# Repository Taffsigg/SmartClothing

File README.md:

# SmartClothing
the shirt that detects heart attacks

//short description of project

//file directory links

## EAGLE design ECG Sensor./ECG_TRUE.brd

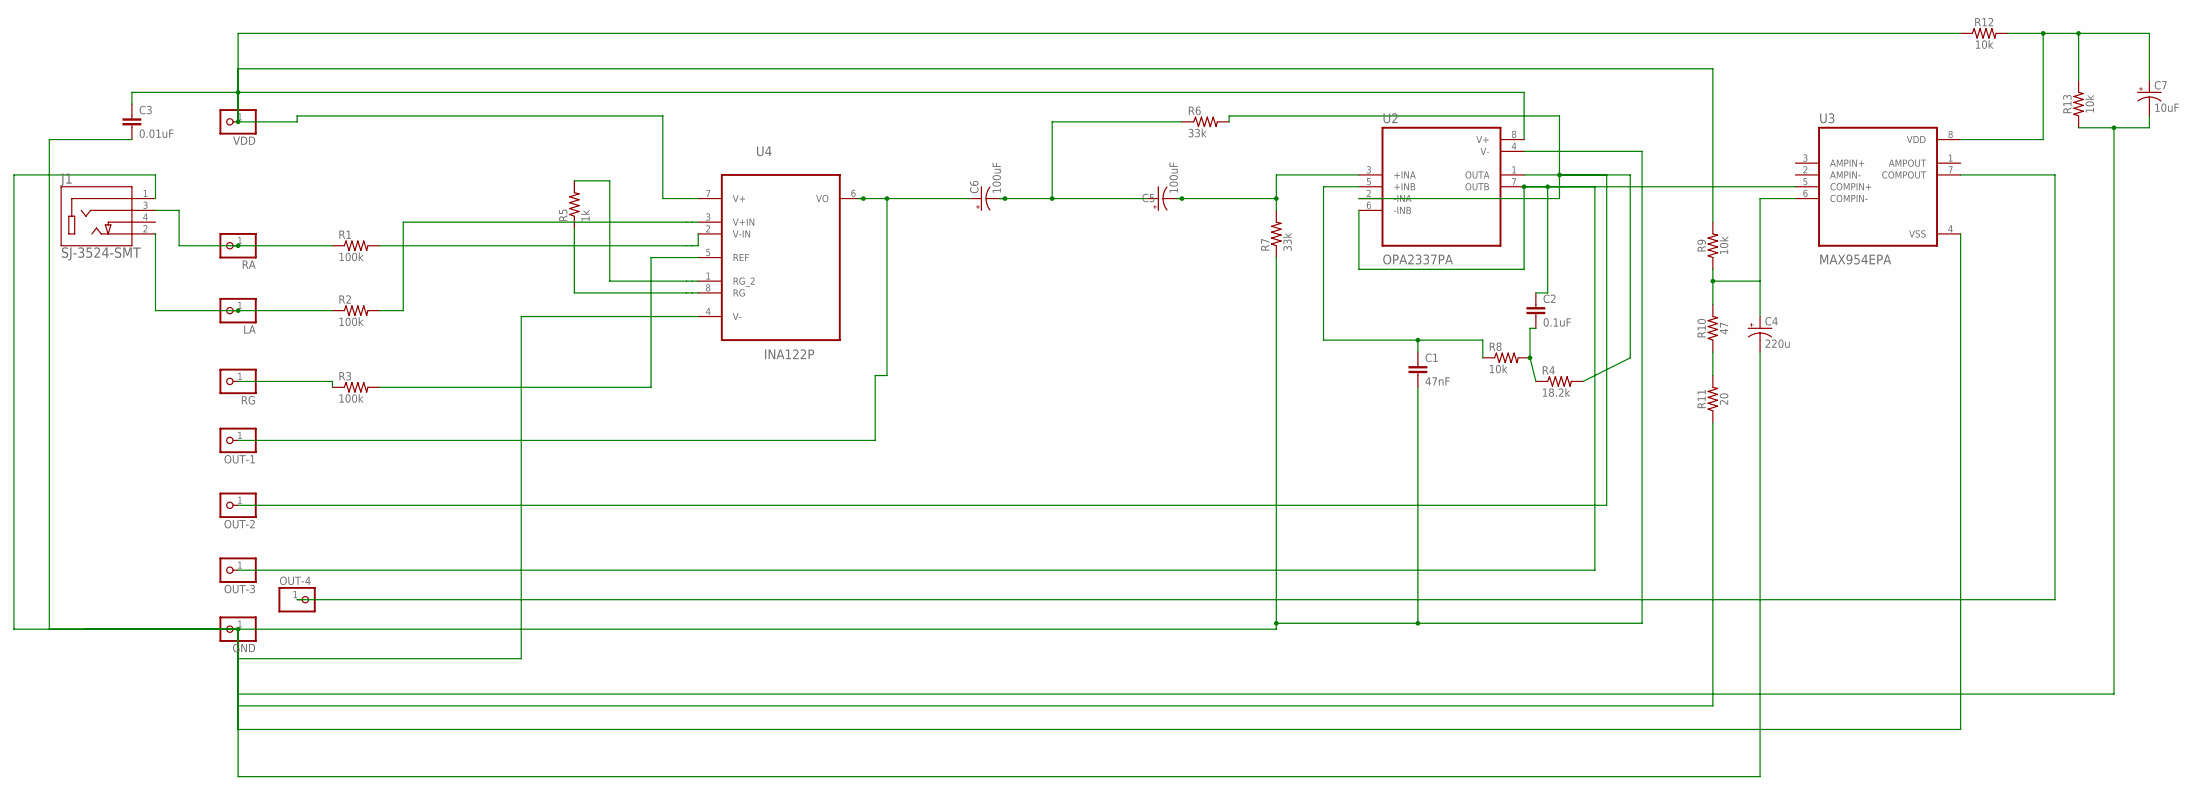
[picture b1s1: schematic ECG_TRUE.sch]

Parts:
C1: 47nF; CAP-PTH-SMALL-KIT
C2: 0.1uF; CAP-PTH-SMALL-KIT
C3: 0.01uF; CAP-PTH-SMALL-KIT
C4: 220u; E3,5-10
C5, C6: 100uF; CPOL-RADIAL-2.5MM-6.5MM
C7: 10uF; CPOL-RADIAL-2.5MM-5MM-KIT
GND: PINHD-1X1; 1X01
J1: SJ-3524-SMT; CUI_SJ-3524-SMT
LA: PINHD-1X1; 1X01
OUT-1, OUT-2, OUT-3, OUT-4: PINHD-1X1; 1X01
R1, R2, R3: 100k; AXIAL-0.3-KIT
R4: 18.2k; AXIAL-0.3-KIT
R5: 1k; AXIAL-0.3-KIT
R6, R7: 33k; AXIAL-0.3-KIT
R8, R9: 10k; AXIAL-0.3-KIT
R10: 47; AXIAL-0.3-KIT
R11: 20; AXIAL-0.3-KIT
R12, R13: 10k; AXIAL-0.3
RA: PINHD-1X1; 1X01
RG: PINHD-1X1; 1X01
U2: OPA2337PA; DIP794W45P254L1060H508Q8
U3: MAX954EPA; DIP794W47P254L991H457Q8
U4: INA122P; DIP254P762X508-8
VDD: PINHD-1X1; 1X01

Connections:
unnamed: J1.3, R1.P$1 (1), RA.1
unnamed: C7.1 (+), R12.P$2 (2), R13.P$2 (2), U3.8 (VDD)
unnamed: C2.2, R4.P$1 (1), R8.P$2 (2)
unnamed: R1.P$2 (2), U4.2 (V-IN)
unnamed: R2.P$2 (2), U4.3 (V+IN)
unnamed: R3.P$1 (1), RG.1
unnamed: R3.P$2 (2), U4.5 (REF)
unnamed: C6.1 (+), OUT-1.1, U4.6 (VO)
unnamed: R5.P$2 (2), U4.1 (RG_2)
unnamed: R5.P$1 (1), U4.8 (RG)
unnamed: C5.1 (+), C6.2 (-), R6.P$1 (1)
unnamed: C5.2 (-), R7.P$2 (2), U2.3 (+INA)
unnamed: OUT-2.1, R4.P$2 (2), R6.P$2 (2), U2.1 (OUTA), U2.2 (-INA)
unnamed: C3.1, R9.P$2 (2), R12.P$1 (1), U2.8 (V+), U4.7 (V+), VDD.1
unnamed: C2.1, OUT-3.1, U2.6 (-INB), U2.7 (OUTB), U3.5 (COMPIN+)
unnamed: R10.P$1 (1), R11.P$2 (2)
unnamed: C1.1, R8.P$1 (1), U2.5 (+INB)
unnamed: C4.+, R9.P$1 (1), R10.P$2 (2), U3.6 (COMPIN-)
unnamed: OUT-4.1, U3.7 (COMPOUT)
unnamed: J1.2, LA.1, R2.P$1 (1)
unnamed: C1.2, C3.2, C4.-, C7.2 (-), GND.1, J1.1, R7.P$1 (1), R11.P$1 (1), R13.P$1 (1), U2.4 (V-), U3.4 (VSS), U4.4 (V-)

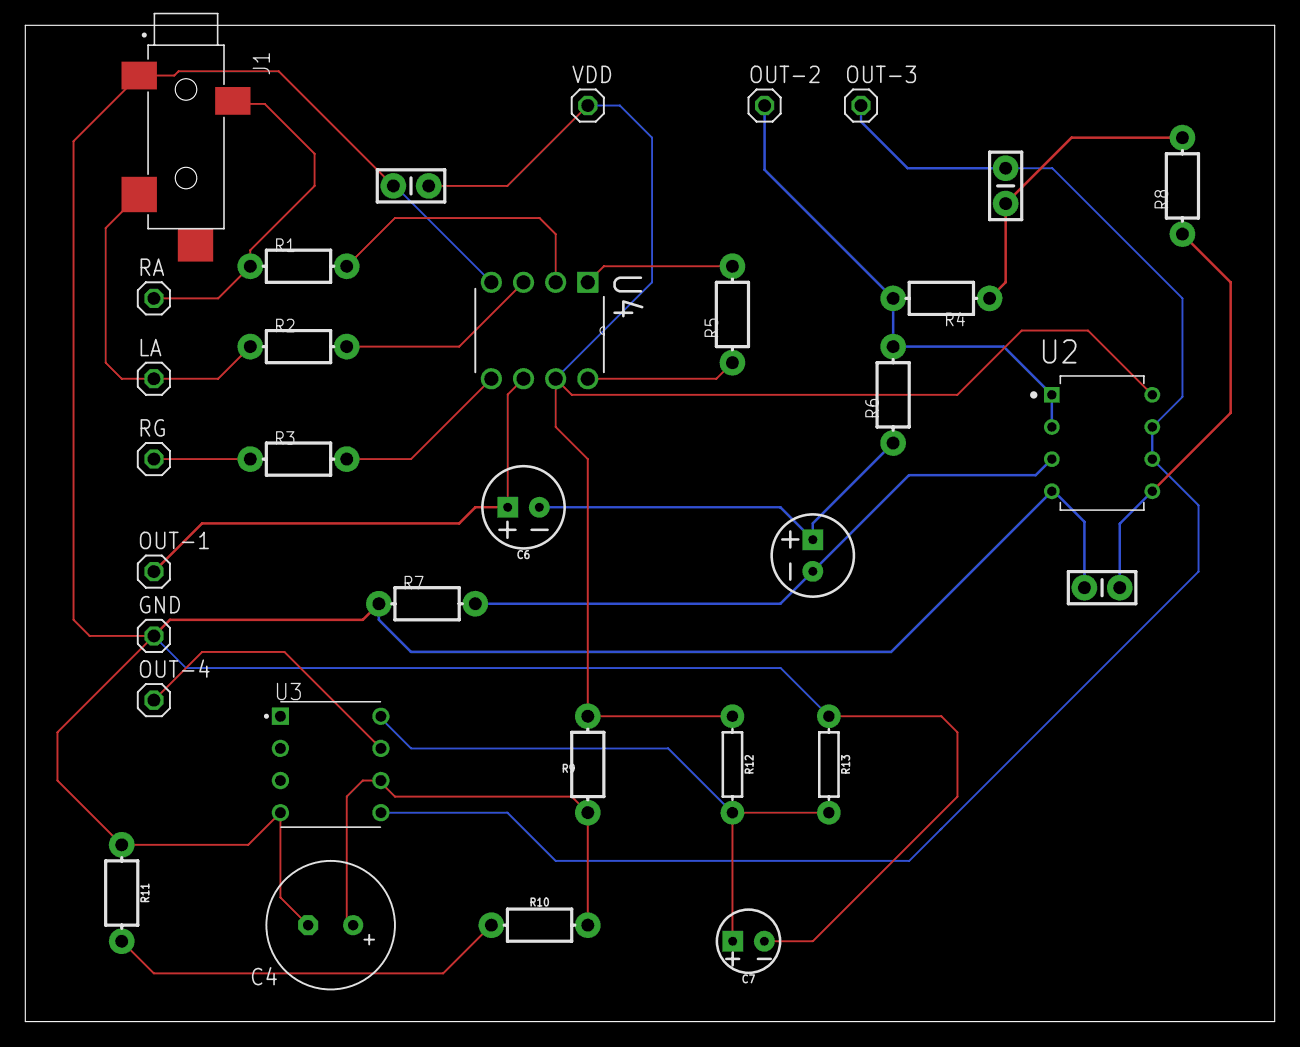
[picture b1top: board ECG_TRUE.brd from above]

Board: 2 copper layers, 98.7 x 78.7 mm, 33 parts (0 on the bottom side), 21 nets.

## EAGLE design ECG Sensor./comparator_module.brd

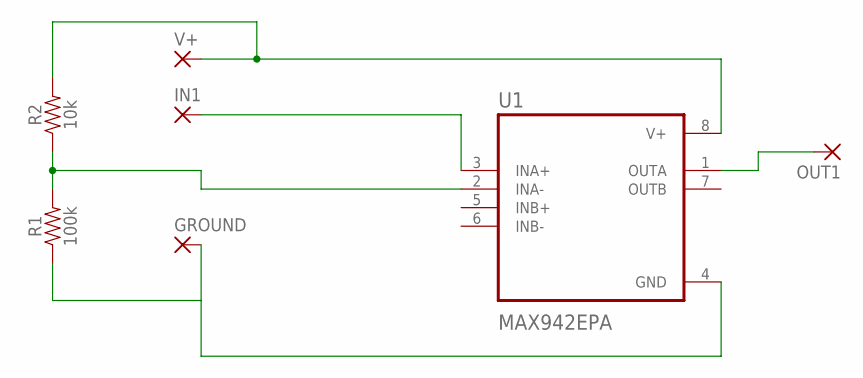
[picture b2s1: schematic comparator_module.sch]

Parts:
GROUND: 3,81/1,4
IN1: 3,81/1,4
OUT1: 3,81/1,4
R1: 100k; AXIAL-0.3
R2: 10k; AXIAL-0.3
U1: MAX942EPA; DIP794W47P254L991H457Q8
V+: 3,81/1,4

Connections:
unnamed: OUT1.1, U1.1 (OUTA)
unnamed: IN1.1, U1.3 (INA+)
unnamed: GROUND.1, R1.P$1 (1), U1.4 (GND)
unnamed: R1.P$2 (2), R2.P$1 (1), U1.2 (INA-)
unnamed: R2.P$2 (2), U1.8 (V+), V+.1

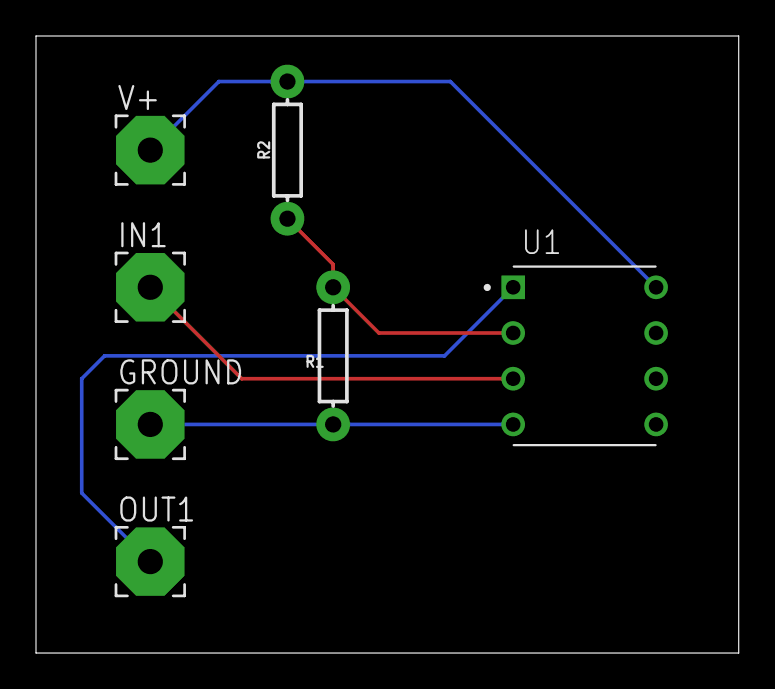
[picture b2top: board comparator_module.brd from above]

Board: 2 copper layers, 39.0 x 34.3 mm, 7 parts (0 on the bottom side), 5 nets.

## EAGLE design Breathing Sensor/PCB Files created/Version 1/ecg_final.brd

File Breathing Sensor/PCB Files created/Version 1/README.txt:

modified into version 2 after breadboarding

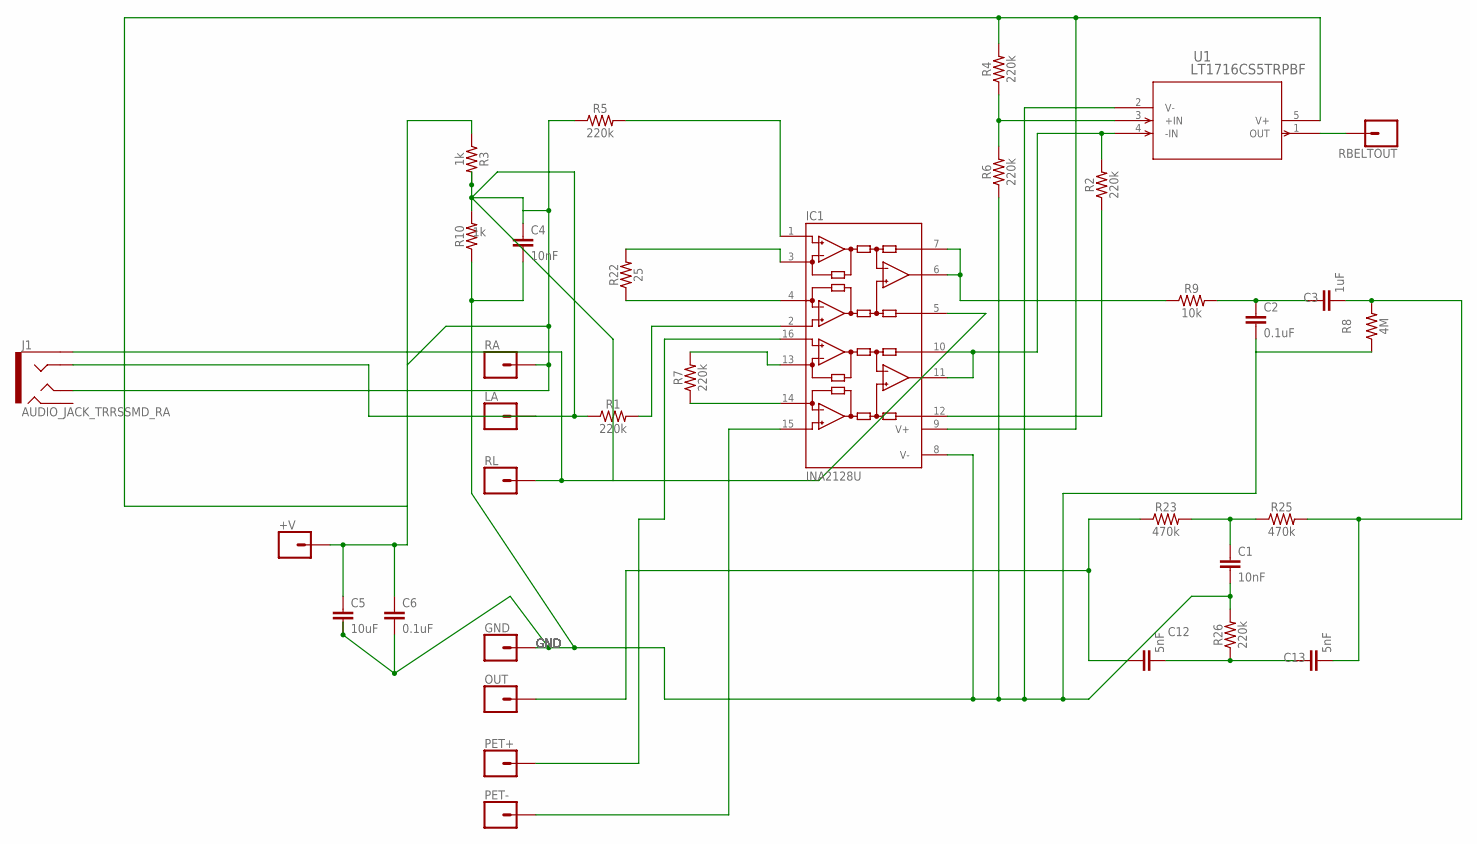
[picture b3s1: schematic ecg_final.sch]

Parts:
+V: CONN_01; 1X01
C1, C4: 10nF; CAP-PTH-10MM
C2, C6: 0.1uF; CAP-PTH-10MM
C3: 1uF; CAP-PTH-10MM
C5: 10uF; CAP-PTH-10MM
C12, C13: 5nF; CAP-PTH-10MM
GND: CONN_01; 1X01
IC1: INA2128U; SO16-1
J1: AUDIO_JACK_TRRSSMD_RA; AUDIO_JACK_3.5MM_TRRS_SMD_RA
LA: CONN_01; 1X01
OUT: CONN_01; 1X01
PET+: CONN_01; 1X01
PET-: CONN_01; 1X01
R1, R2, R4, R5, R6, R7, R26: 220k; AXIAL-0.3
R3, R10: 1k; AXIAL-0.3
R8: 4M; AXIAL-0.3
R9: 10k; AXIAL-0.3
R22: 25; AXIAL-0.3
R23, R25: 470k; AXIAL-0.3
RA: CONN_01; 1X01
RBELTOUT: CONN_01; 1X01
RL: CONN_01; 1X01
U1: LT1716CS5TRPBF; SOT-5_S

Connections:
+V: +V.1, C5.1, C6.1, IC1.9 (V+), R3.P$1 (1), R4.P$2 (2), U1.5 (V+)
GND: C1.2, C2.2, C4.2, C5.2, C6.2, GND.1, IC1.8 (V-), R6.P$1 (1), R8.P$1 (1), R10.P$1 (1), R26.P$2 (2), U1.2 (V-)
LAA: IC1.2 (INA+), R1.P$2 (2)
unnamed: C12.2, C13.1, R26.P$1 (1)
unnamed: IC1.6 (VOA), IC1.7 (SENSEA), R9.P$1 (1)
unnamed: IC1.4 (RGA), R22.P$1 (1)
unnamed: C2.1, C3.1, R9.P$2 (2)
unnamed: IC1.1 (INA-), R5.P$2 (2)
unnamed: IC1.10 (SENSEB), IC1.11 (VOB), R2.P$2 (2), U1.4 (-IN)
unnamed: IC1.16 (INB-), PET+.1
unnamed: IC1.12 (REFB), R2.P$1 (1)
unnamed: C1.1, R23.P$2 (2), R25.P$1 (1)
unnamed: R4.P$1 (1), R6.P$2 (2), U1.3 (+IN)
unnamed: C3.2, C13.2, R8.P$2 (2), R25.P$2 (2)
unnamed: IC1.13 (RGB), R7.P$2 (2)
unnamed: IC1.14 (RGB), R7.P$1 (1)
unnamed: IC1.15 (INB+), PET-.1
unnamed: RBELTOUT.1, U1.1 (OUT)
unnamed: IC1.3 (RGA), R22.P$2 (2)
OUT: C12.1, OUT.1, R23.P$1 (1)
RL: C4.1, IC1.5 (REFA), J1.EARTH, J1.RING1, J1.TIP, LA.1, R1.P$1 (1), R3.P$2 (2), R5.P$1 (1), R10.P$2 (2), RA.1, RL.1

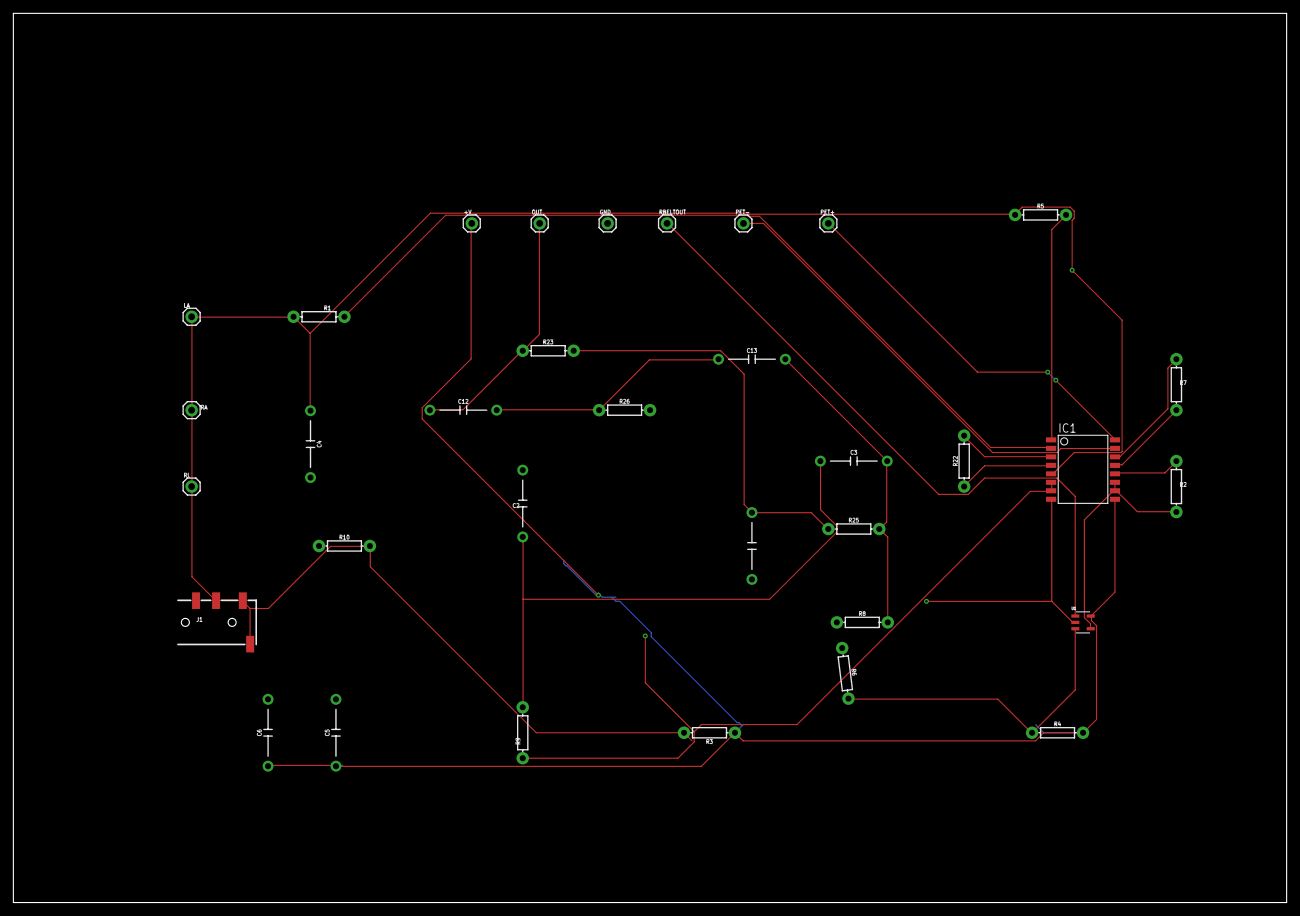
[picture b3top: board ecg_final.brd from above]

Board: 2 copper layers, 190.5 x 133.0 mm, 34 parts (0 on the bottom side), 21 nets.

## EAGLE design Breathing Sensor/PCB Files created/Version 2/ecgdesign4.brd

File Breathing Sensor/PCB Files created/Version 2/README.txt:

scrapped because SMD chips are garbage and I hate them.

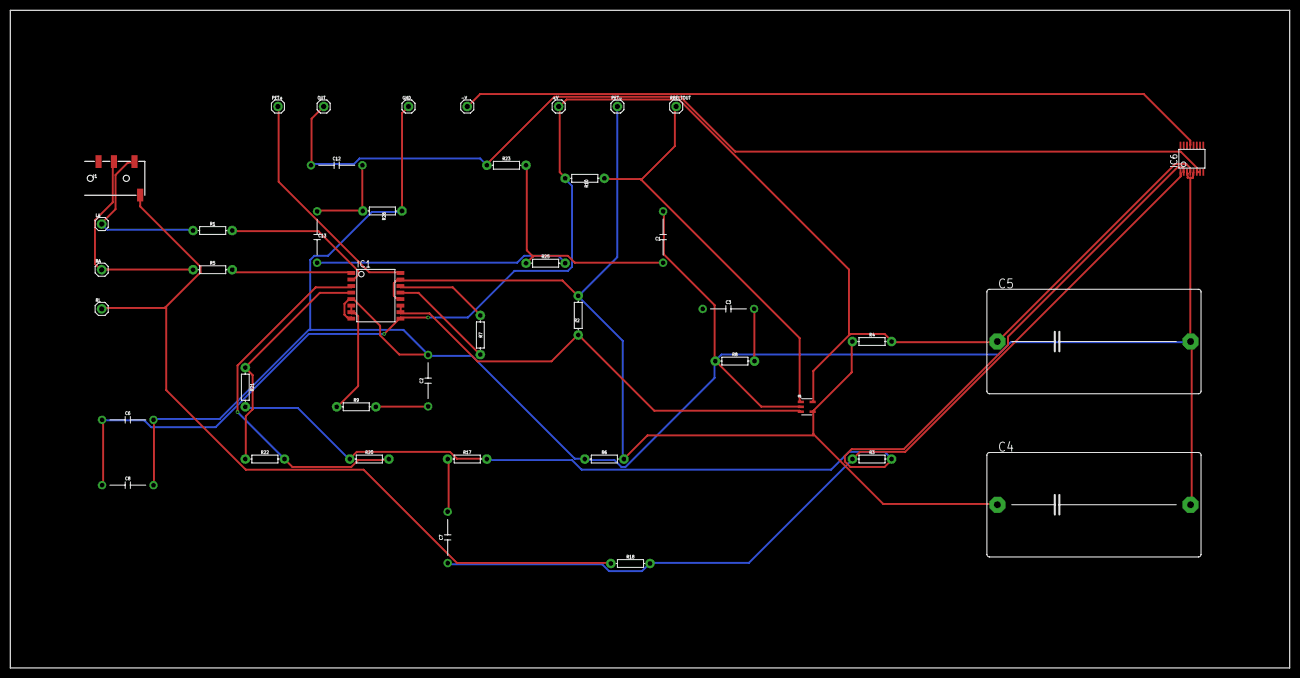
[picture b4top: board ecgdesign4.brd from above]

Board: 2 copper layers, 248.9 x 127.9 mm, 42 parts (0 on the bottom side), 26 nets.

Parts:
+V: 1X01
-V: 1X01
C1, C2, C3: 10nF; CAP-PTH-10MM
C4, C5: 20u; C37.5B20
C6: 10uF; CAP-PTH-10MM
C7, C8: 0.1uF; CAP-PTH-10MM
C12, C13: 5nF; CAP-PTH-10MM
GND: 1X01
IC1: INA2128U; SO16-1
IC6: SSOP16BU
J1: AUDIO_JACK_TRRSSMD_RA; AUDIO_JACK_3.5MM_TRRS_SMD_RA
LA: 1X01
OUT: 1X01
PET+: 1X01
PET-: 1X01
R1, R5, R18, R26: 220k; AXIAL-0.3
R2: 100k; AXIAL-0.3
R3: 1M; AXIAL-0.3
R4, R6, R17: 10k; AXIAL-0.3
R7, R8, R9: 1k; AXIAL-0.3
R10: 20k; AXIAL-0.3
R20, R21: 22k; AXIAL-0.3
R22: 25; AXIAL-0.3
R23, R25: 470k; AXIAL-0.3
RA: 1X01
RBELTOUT: 1X01
RL: 1X01
U1: LT1716CS5TRPBF; SOT-5_S

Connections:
+V: +V.1, C5.1, C6.1, C8.1, IC1.9, IC6.4, R4.P$2, R10.P$2, U1.5
-V: -V.1, IC6.13
GND: C1.2, C2.2, C4.2, C5.2, C6.2, C8.2, GND.1, IC1.5, IC1.8, IC6.3, IC6.5, R6.P$1, R8.P$1, R26.P$1, U1.2
LAA: IC1.2, R1.P$2
unnamed: IC1.14, R7.P$1
unnamed: J1.TIP, LA.1, R1.P$1
unnamed: C7.2, R17.P$1
unnamed: IC1.6, IC1.7, R9.P$1
unnamed: C7.1, IC6.1, R3.P$1, R18.P$2
unnamed: IC6.2, R3.P$2, R17.P$2, R20.P$1, R21.P$2
unnamed: C12.2, C13.1, R26.P$2
unnamed: IC1.4, R21.P$1, R22.P$1
unnamed: C2.1, R9.P$2
unnamed: IC1.1, R5.P$2
unnamed: C3.2, R8.P$2
unnamed: IC1.13, R7.P$2
unnamed: IC1.10, IC1.11, R2.P$2, U1.3
unnamed: C4.1, IC1.12, IC1.15, PET-.1, R2.P$1, R4.P$1, R6.P$2, U1.4
unnamed: J1.EARTH, R18.P$1, RL.1
unnamed: C1.1, R23.P$2, R25.P$1
unnamed: IC1.16, PET+.1
unnamed: C13.2, R25.P$2
unnamed: J1.RING1, R5.P$1, RA.1
unnamed: R10.P$1, RBELTOUT.1, U1.1
unnamed: IC1.3, R20.P$2, R22.P$2
OUT: C12.1, IC6.6, IC6.7, OUT.1, R23.P$1

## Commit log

2019-08-29 Folders and Outline
    Created Folders and outline for readme
2019-08-29 Adding previous PCB designs
    breathing sensor PCB models
2019-08-29 fixed file name typo
2019-09-12 Create ECGSensor
2019-09-12 Update ECGSensor
2019-10-09 OBEX Object Push
2019-11-18 Create ECG Subsystem
2019-11-18 Create ECG Schematic
2019-11-18 Rename ECG Schematic to ECG Schematic.md
2019-11-20 Eagle PCB/Schematic
2019-11-20 Rename ECG Sensor./ECG_TRUE.brd to ECG Sensor/SCHEMATICS/ECG_TRUE.brd

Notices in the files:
parts and their libraries:
SparkFun-Connectors: Licensing: Creative Commons ShareAlike 4.0 International - https://creativecommons.org/licenses/by-sa/4.0
